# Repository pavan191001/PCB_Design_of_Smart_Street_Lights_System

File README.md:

# Electronics Packaging 
To build a PCB that performs motion sensor-based light system using Autocad Eagle

Group Members: 

      1.  K Sreenivasulu Reddy(S20190020217)

      2.  Kakarla V S S Pavan Teja(S20190020216)

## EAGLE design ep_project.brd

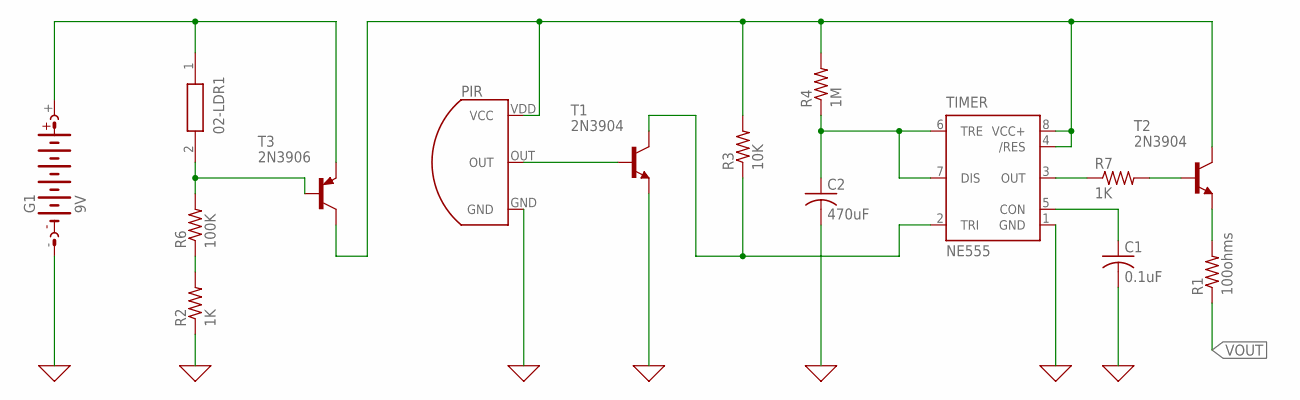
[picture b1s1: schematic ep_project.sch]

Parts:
C1: 0.1uF; C025-024X044; MPN C0603C104M4RACTU.
C2: 470uF; C025-024X044; MPN 477CKE016M .
G1: 9V; AB9V; MPN 1294
PIR: EKMC4607112k; TO-3; MPN EKMC1603111
R1: 100ohms; M0805; MPN MCMF0W4FF1000A50
R2, R7: 1K; M0805; MPN YR1B1K0CC
R3: 10K; M0805; MPN YR1B10KCC
R4: 1M; M0805; MPN MBB02070C1004FC100
R5: 02-LDR1; 02LDR1; MPN VT935G
R6: 100K; M0805; MPN MCMF0W2FF1003A10
T1, T2: 2N3904; TO92; MPN 2N3904TFR.
T3: 2N3906; TO92; MPN 2N3906
TIMER: NE555; DIL-08

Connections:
0: C1.2, C2.2, G1.-, PIR.GND, R2.1, T1.3 (E), TIMER.1 (GND)
unnamed: G1.+, R5.1, T3.3 (E)
unnamed: R5.2, R6.2, T3.2 (B)
unnamed: R2.2, R6.1
unnamed: R3.1, T1.1 (C), TIMER.2 (TRI)
unnamed: PIR.VDD (VCC), R3.2, R4.2, T2.1 (C), T3.1 (C), TIMER.4 (/RES), TIMER.8 (VCC+)
unnamed: PIR.OUT, T1.2 (B)
unnamed: C2.1, R4.1, TIMER.6 (TRE), TIMER.7 (DIS)
unnamed: R1.2, T2.3 (E)
unnamed: R7.1, TIMER.3 (OUT)
unnamed: R7.2, T2.2 (B)
unnamed: C1.1, TIMER.5 (CON)
VOUT: R1.1

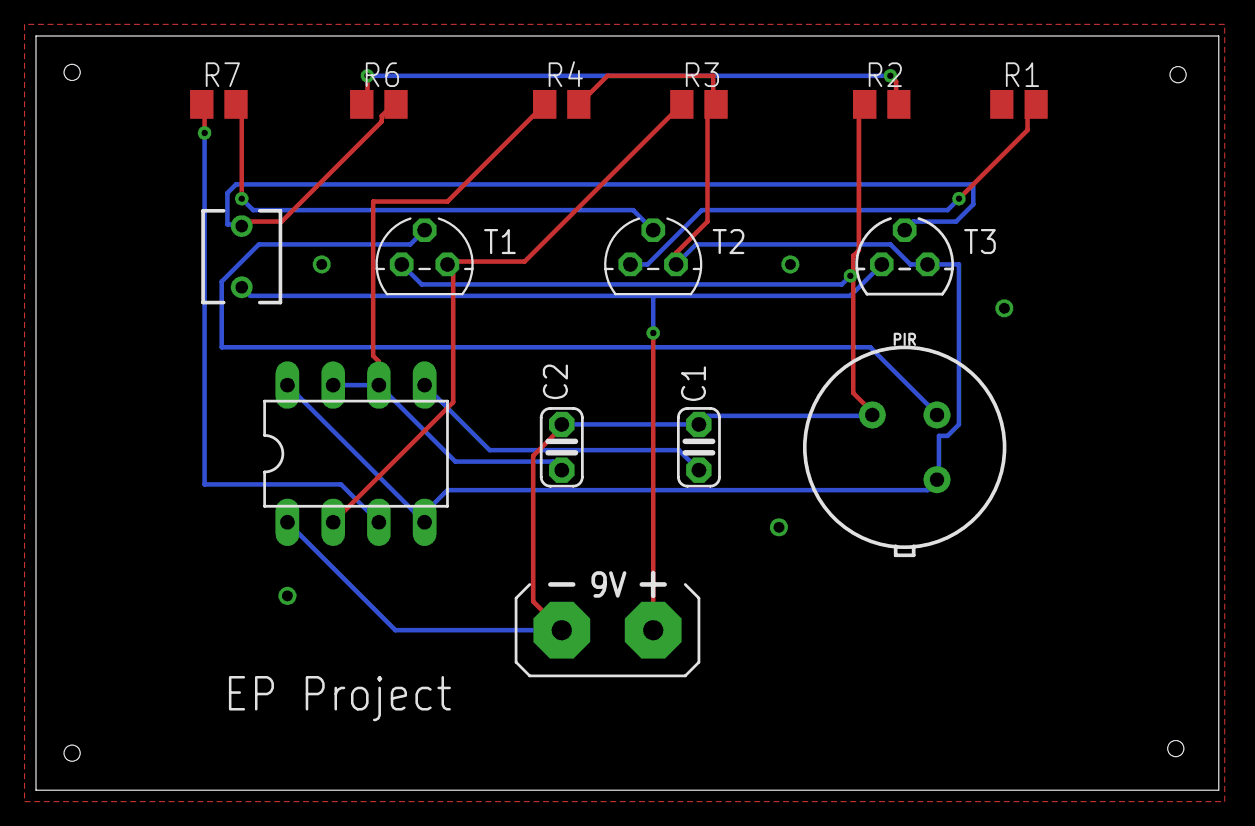
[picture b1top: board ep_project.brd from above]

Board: 2 copper layers, 65.7 x 41.9 mm, 15 parts (0 on the bottom side), 12 nets.

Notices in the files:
parts and their libraries:
Library: Licensing: Creative Commons ShareAlike 4.0 International - https://creativecommons.org/licenses/by-sa/4.0
